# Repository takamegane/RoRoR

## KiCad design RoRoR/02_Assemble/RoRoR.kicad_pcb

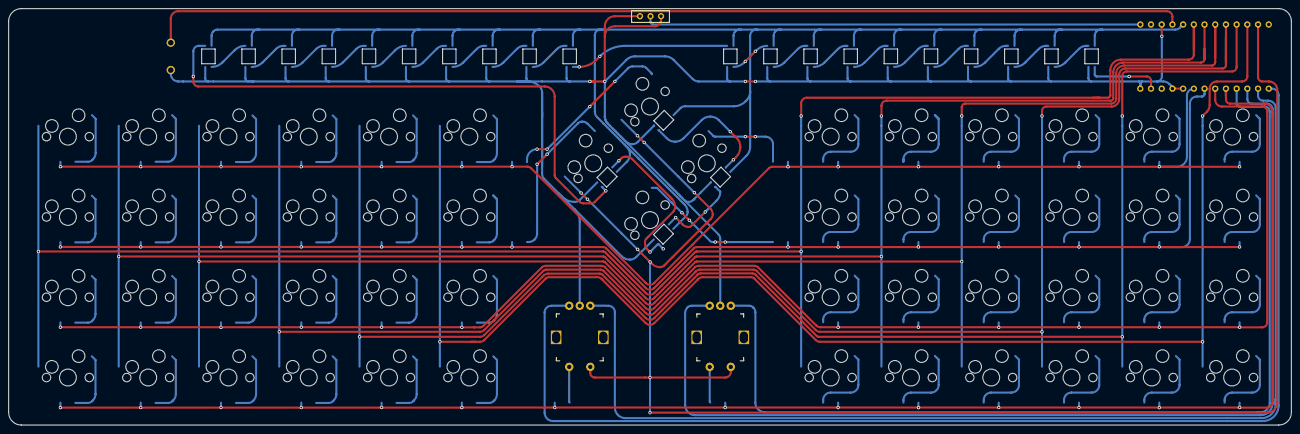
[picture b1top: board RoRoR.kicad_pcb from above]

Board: 2 copper layers, 304.4 x 98.8 mm, 135 parts (0 on the bottom side), 97 nets.

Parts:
D1, D2, D3, D4, D5, D6, D7, D8, D9, D10, D11, D12, D13, D14, D15, D16, D17, D18, D19, D20, D21, D22, D23, D24, D25, D26, D27, D28, D29, D30, D31, D32, D33, D34, D35, D36, D37, D38, D39, D40, D41, D42, D43, D44, D45, D46, D47, D48, D49, D50, D51, D52, D53, D54: D; Diode_SMD
J1: Conn_01x02; Battery_XH2.5_GL_PCB
L1, L2, L3, L4, L5, L6, L7, L8, L9, L10, L11, L12, L13, L14, L15, L16, L17, L18, L19, L20, L21, L22, L23, L24: SK6812MINI; LED_SK6812MINI-E_BL
SW1, SW2, SW3, SW4, SW5, SW6, SW7, SW8, SW9, SW10, SW11, SW12, SW13, SW14, SW15, SW16, SW17, SW18, SW19, SW20, SW21, SW22, SW23, SW24, SW25, SW26, SW28, SW29, SW30, SW31, SW32, SW33, SW34, SW35, SW36, SW37, SW38, SW39, SW40, SW41, SW42, SW43, SW44, SW45, SW46, SW47, SW48, SW49, SW50, SW51, SW52, SW53: SW_PUSH; CherryMX_Hotswap_1u
SW27, SW54: RotaryEncoder_Switch; RotaryEncoder_EC12E
SW55: SW_PUSH; ResetSW
U1: BLEMicroPro; Micon_BMP_GL

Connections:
A1: SW27.A, U1.11 (B4/PIN11)
A2: SW54.A, U1.9 (D7/PIN9)
B1: SW27.B, U1.12 (B5/PIN12)
B2: SW54.B, U1.10 (E6/PIN10)
Bat+: J1.1, U1.25 (BAT+)
Col0: SW1.1, SW2.1, SW3.1, SW4.1, SW28.1, SW29.1, SW30.1, SW31.1, U1.20 (F4/PIN20)
Col1: SW5.1, SW6.1, SW7.1, SW8.1, SW32.1, SW33.1, SW34.1, SW35.1, U1.19 (F5/PIN19)
Col2: SW9.1, SW10.1, SW11.1, SW12.1, SW36.1, SW37.1, SW38.1, SW39.1, U1.18 (F6/PIN18)
Col3: SW13.1, SW14.1, SW15.1, SW16.1, SW40.1, SW41.1, SW42.1, SW43.1, U1.17 (F7/PIN17)
Col4: SW17.1, SW18.1, SW19.1, SW20.1, SW44.1, SW45.1, SW46.1, SW47.1, U1.16 (B1/PIN16)
Col5: SW21.1, SW22.1, SW23.1, SW24.1, SW48.1, SW49.1, SW50.1, SW51.1, U1.15 (B3/PIN15)
Col6: SW25.1, SW26.1, SW27.S2, SW52.1, SW53.1, SW54.S2, U1.14 (B2/PIN14)
GND: J1.2, L1.2 (VSS), L2.2 (VSS), L3.2 (VSS), L4.2 (VSS), L5.2 (VSS), L6.2 (VSS), L7.2 (VSS), L8.2 (VSS), L9.2 (VSS), L10.2 (VSS), L11.2 (VSS), L12.2 (VSS), L13.2 (VSS), L14.2 (VSS), L15.2 (VSS), L16.2 (VSS), L17.2 (VSS), L18.2 (VSS), L19.2 (VSS), L20.2 (VSS), L21.2 (VSS), L22.2 (VSS), L23.2 (VSS), L24.2 (VSS), SW27.C, SW54.C, SW55.2, U1.3 (GND), U1.4 (GND), U1.23 (GND), U1.26 (BAT-)
LED: L1.3 (DIN), U1.1 (D3/PIN1)
unnamed: D1.2 (A), SW1.2
unnamed: D2.2 (A), SW2.2
unnamed: D3.2 (A), SW3.2
unnamed: D4.2 (A), SW4.2
unnamed: D5.2 (A), SW5.2
unnamed: D6.2 (A), SW6.2
unnamed: D7.2 (A), SW7.2
unnamed: D8.2 (A), SW8.2
unnamed: D9.2 (A), SW9.2
unnamed: D10.2 (A), SW10.2
unnamed: D11.2 (A), SW11.2
unnamed: D12.2 (A), SW12.2
unnamed: D13.2 (A), SW13.2
unnamed: D14.2 (A), SW14.2
unnamed: D15.2 (A), SW15.2
unnamed: D16.2 (A), SW16.2
unnamed: D17.2 (A), SW17.2
unnamed: D18.2 (A), SW18.2
unnamed: D19.2 (A), SW19.2
unnamed: D20.2 (A), SW20.2
unnamed: D21.2 (A), SW21.2
unnamed: D22.2 (A), SW22.2
unnamed: D23.2 (A), SW23.2
unnamed: D24.2 (A), SW24.2
unnamed: D25.2 (A), SW25.2
unnamed: D26.2 (A), SW26.2
unnamed: D27.2 (A), SW27.S1
unnamed: D28.1 (K), SW28.2
unnamed: D29.1 (K), SW29.2
unnamed: D30.1 (K), SW30.2
unnamed: D31.1 (K), SW31.2
unnamed: D32.1 (K), SW32.2
unnamed: D33.1 (K), SW33.2
unnamed: D34.1 (K), SW34.2
unnamed: D35.1 (K), SW35.2
unnamed: D36.1 (K), SW36.2
unnamed: D37.1 (K), SW37.2
unnamed: D38.1 (K), SW38.2
unnamed: D39.1 (K), SW39.2
unnamed: D40.1 (K), SW40.2
unnamed: D41.1 (K), SW41.2
unnamed: D42.1 (K), SW42.2
unnamed: D43.1 (K), SW43.2
unnamed: D44.1 (K), SW44.2
unnamed: D45.1 (K), SW45.2
unnamed: D46.1 (K), SW46.2
unnamed: D47.1 (K), SW47.2
unnamed: D48.1 (K), SW48.2
unnamed: D49.1 (K), SW49.2
unnamed: D50.1 (K), SW50.2
unnamed: D51.1 (K), SW51.2
unnamed: D52.1 (K), SW52.2
unnamed: D53.1 (K), SW53.2
unnamed: D54.1 (K), SW54.S1
unnamed: L1.1 (DOUT), L2.3 (DIN)
unnamed: L2.1 (DOUT), L3.3 (DIN)
unnamed: L3.1 (DOUT), L4.3 (DIN)
unnamed: L4.1 (DOUT), L5.3 (DIN)
unnamed: L5.1 (DOUT), L6.3 (DIN)
unnamed: L6.1 (DOUT), L7.3 (DIN)
unnamed: L7.1 (DOUT), L8.3 (DIN)
unnamed: L8.1 (DOUT), L9.3 (DIN)
unnamed: L10.1 (DOUT), L11.3 (DIN)
unnamed: L9.1 (DOUT), L10.3 (DIN)
unnamed: L11.1 (DOUT), L12.3 (DIN)
unnamed: L12.1 (DOUT), L13.3 (DIN)
unnamed: L13.1 (DOUT), L14.3 (DIN)
unnamed: L14.1 (DOUT), L15.3 (DIN)
unnamed: L15.1 (DOUT), L16.3 (DIN)
unnamed: L16.1 (DOUT), L17.3 (DIN)
unnamed: L17.1 (DOUT), L18.3 (DIN)
unnamed: L18.1 (DOUT), L19.3 (DIN)
unnamed: L19.1 (DOUT), L20.3 (DIN)
unnamed: L20.1 (DOUT), L21.3 (DIN)
unnamed: L21.1 (DOUT), L22.3 (DIN)
unnamed: L22.1 (DOUT), L23.3 (DIN)
unnamed: L23.1 (DOUT), L24.3 (DIN)
Reset: SW55.1, U1.22 (RST)
Row0: D1.1 (K), D5.1 (K), D9.1 (K), D13.1 (K), D17.1 (K), D21.1 (K), D25.1 (K), D28.2 (A), D32.2 (A), D36.2 (A), D40.2 (A), D44.2 (A), D48.2 (A), D52.2 (A), U1.5 (D1/PIN5/SDA)
Row1: D2.1 (K), D6.1 (K), D10.1 (K), D14.1 (K), D18.1 (K), D22.1 (K), D26.1 (K), D29.2 (A), D33.2 (A), D37.2 (A), D41.2 (A), D45.2 (A), D49.2 (A), D53.2 (A), U1.6 (D0/PIN6/SCL)
Row2: D3.1 (K), D7.1 (K), D11.1 (K), D15.1 (K), D19.1 (K), D23.1 (K), D30.2 (A), D34.2 (A), D38.2 (A), D42.2 (A), D46.2 (A), D50.2 (A), U1.7 (D4/PIN7)
Row3: D4.1 (K), D8.1 (K), D12.1 (K), D16.1 (K), D20.1 (K), D24.1 (K), D27.1 (K), D31.2 (A), D35.2 (A), D39.2 (A), D43.2 (A), D47.2 (A), D51.2 (A), D54.2 (A), U1.8 (C6/PIN8)
VCC: L1.4 (VDD), L2.4 (VDD), L3.4 (VDD), L4.4 (VDD), L5.4 (VDD), L6.4 (VDD), L7.4 (VDD), L8.4 (VDD), L9.4 (VDD), L10.4 (VDD), L11.4 (VDD), L12.4 (VDD), L13.4 (VDD), L14.4 (VDD), L15.4 (VDD), L16.4 (VDD), L17.4 (VDD), L18.4 (VDD), L19.4 (VDD), L20.4 (VDD), L21.4 (VDD), L22.4 (VDD), L23.4 (VDD), L24.4 (VDD), U1.21 (VCC)

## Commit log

2022-02-18 upload
2022-02-19 03 deco upload
2022-02-22 rename
2022-05-24 Create LICENSE
2024-04-25 all data replacement
